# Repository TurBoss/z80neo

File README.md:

# z80neo

```

          ████   ████                             
         █░░░ █ █░░░██                            
  ██████░█   ░█░█  █░█ ███████   █████   ██████   
 ░░░░██ ░ ████ ░█ █ ░█░░██░░░██ ██░░░██ ██░░░░██  
    ██   █░░░ █░██  ░█ ░██  ░██░███████░██   ░██  
   ██   ░█   ░█░█   ░█ ░██  ░██░██░░░░ ░██   ░██  
  ██████░ ████ ░ ████  ███  ░██░░██████░░██████   
 ░░░░░░  ░░░░   ░░░░  ░░░   ░░  ░░░░░░  ░░░░░░    

```

**A computer built around a real Z80 CPU.**

z80neo is not an emulator. A genuine Zilog **Z0840004** (NMOS, TTL-level)
runs real code, while an Olimex **RP2350-PICO2-BB48** (RP2350**B**, 48 GPIOs)
acts as its RAM, ROM and *all* of its I/O. The Pico captures the Z80 bus
cycle-by-cycle through PIO, services each access and stalls the CPU with
`WAIT` — so the two chips share one bus exactly like a classic microcomputer.

On top of that it emulates an MMU, a serial console (and a second UART), a
15-drive CP/M sector disk, an OLED status display, a keypad menu, and it
drives an optional FPGA VDP over SPI. It boots **CP/M 2.2**, **Fuzix** and
bare-metal Z80 programs from an SD card.

- Website / source: https://github.com/turboss/z80neo
- Console: **UART0, 115200 8N1** (GPIO0/1), shared by the firmware and CP/M
- Storage: SD card (FatFS) holding the OS images, disk images and `Z80NEO.INI`

## Features

- **Real Z80, no emulation** — the Pico is bus master/slave only; the Z80
  executes every instruction.
- **Full memory + MMU** — four 16 KB banks (`ram[4][16384]`), optionally
  extended with PSRAM, behind a 4-page MMU on ports `0xF0`–`0xF3`.
- **Serial console** on UART0 (`0x80`/`0x81`) plus an independent second UART
  (UART1, `0x90`–`0x93`) with runtime-configurable baud/format.
- **CP/M 2.2** with 15 emulated sector disks (A:–O:) from `CPMDISK0..14.IMG`.
- **SD-card file API** for bare-metal programs (`0xA0`–`0xA7`), with directory
  walking into subdirectories.
- **Firmware-side Standard MIDI File player** streaming to a UART1 MIDI out,
  with a live VT102 channel monitor.
- **SSD1306 OLED status display + ADC keypad menu**, with an idle screensaver.
- **VoidVDP / NullVDP support** — a 640×256 bitmap console with an `ESC g`
  protocol, mirrored over SPI to an FPGA VDP.

## Hardware

- CPU: Zilog **Z0840004** (NMOS Z80, 4 MHz rated, run at ~128 kHz)
- Host: Olimex **RP2350-PICO2-BB48** (RP2350B, 48-GPIO package, 16 MB flash)
- Z80 clock generated by PIO on **GPIO32**, reset on **GPIO33**
- SD card interface
- Serial port (UART0, 115200 8N1, GPIO0/1)
- Second UART on **GPIO38 (TX) / GPIO39 (RX)**
- SSD1306 OLED (I2C1) and an ADC keypad
- Optional NullVDP on an FPGA over SPI (GPIO34–37)

Schematics live in `hardware/`; see the pinout and datasheets in `doc/`.

## Schematics

## How it works

- **Bus capture (PIO)** — two PIO0 state machines watch `MREQ` and `IORQ`. On
  a cycle they assert `WAIT`, push a bus snapshot to the FIFO and block on
  `PULL`. The ARM core services the cycle, reads the address/data through the
  `SEL1/2/3` mux and releases `WAIT`. Because the Z80 is stalled for the whole
  service time, timing is independent of the emulated clock speed.
- **Memory / MMU** — `src/memory.c`. 16-bit addresses map through `mmu_page[]`
  into the 16 KB banks; PSRAM can extend them.
- **I/O ports** — handled in `io_read_port()` / `io_write_port()`:

  | Port(s) | Function |
  |---------|----------|
  | `0x80`/`0x83` | console data |
  | `0x81` | console status |
  | `0x90`/`0x91` | UART1 data / status |
  | `0x92`/`0x93` | UART1 baud code / line format config |
  | `0x94`/`0x95` | NullVDP console byte / link status |
  | `0xA0`–`0xA7` | SD-card file API (command, name, data, seek/size) |
  | `0xD1` | I2C EEPROM |
  | `0xE0`–`0xE3` | CP/M disk (data/command, track, sector/status, drive select) |
  | `0xF0`–`0xF3` | MMU page select |

- **Clock / reset** — `src/z80clock.pio` generates the Z80 clock; frequency
  (`Z80_KHZ`, 32..1000) and duty (`Z80_DUTY`, 5..95 %) are settable from
  `Z80NEO.INI`.
- **Display / keys** — core 1 drives the OLED and the debounced ADC keypad
  menu; core 0 owns the bus loop and UARTs.
- **Boot** — mount SD → read `Z80NEO.INI` → load the Intel HEX program into
  banks → hold reset → start PIO → release reset.

See `AGENTS.md` for an in-depth description of every subsystem and the
hardware/timing gotchas.

## Build the firmware

Requires the Raspberry Pi **pico-sdk 2.x** and an `arm-none-eabi` toolchain.
`firmware/build.sh` hardcodes the local SDK paths — edit it for your setup.

```sh
cd firmware
./build.sh            # cmake -B build -S . -DPICO_BOARD=z80neo_bb48 -DPSRAM_ENABLE=ON
```

The output ELF is `firmware/build/z80neo/z80neo.elf`. **Build with
`PICO_BOARD=z80neo_bb48`, never `pico2`** — `pico2` is the RP2350A (30 GPIOs),
so GPIO30–47 (clock, reset, keypad) are silently dropped. `main.c` `#error`s on
the wrong package.

Flash over CMSIS-DAP/OpenOCD:

```sh
cd firmware
./upload.sh           # openocd ... program build/z80neo/z80neo.elf verify reset exit
```

Debug (OpenOCD + GDB):

```sh
cd firmware
./debug.sh            # standard gdbinit
./debug.sh serial     # serial-tracing gdb script
```

There is no unit-test framework; verify by building, flashing and watching
UART0 (115200 8N1) plus the OLED. `tools/z80_boot_sim.py` is the only offline
harness. The full pipeline — firmware + OS + SD deploy — is `./build_all.sh`.

## SD card

Copy `sdcard/Z80NEO.INI`, your program image and the CP/M disk images to the
card root. The preferred INI format is order-independent `KEY=VALUE`:

| Key | Meaning |
|-----|---------|
| `MACHINE` | machine name |
| `CANCEL2`,`CANCEL`,`OK`,`BACK`,`DOWN`,`UP` | ADC keypad thresholds |
| `PROG1`..`PROG4` | program filenames (`PROG1` is loaded at boot) |
| `DEBUG` | `1` = hold in a busy loop at boot |
| `FUZIX` | full-RAM load + hardware `/INT` (Fuzix) |
| `BAUD` | UART0 console baud (default 115200) |
| `UART1_BAUD`, `UART1_FORMAT` | second UART, e.g. `115200` / `8N1` |
| `Z80_KHZ`, `Z80_DUTY` | Z80 clock frequency / duty |
| `MIDI_GROUP_X10`, `MIDI_BYTE_X10` | MIDI player speed trim (tenths of a ms) |
| `MIDI_PANEL` | `1`/`0` firmware MIDI channel monitor |
| `SCREENSAVER`, `SS_MODE`, `SS_IDLE` | idle OLED screensaver settings |

The default `sdcard/Z80NEO.INI` boots CP/M. Program images are Intel HEX —
both the `.hex` (CP/M) and `.ihx` (z88dk) spellings load.

## Software

- **CP/M 2.2** — `software/cpm/z80neo/`, built with `make` into
  `build/cpmz80neo.hex`. CCP/BDOS at `0xD400`, BIOS at `0xEB00`; 15 sector
  disks A:–O: from `CPMDISK0..14.IMG`. CP/M disk helpers live in `tools/`
  (`pack_cpm_collection.py`, `install_cpm_disks.py`) and the PySide6
  `TBCPMTools` GUI can inspect/edit the images.
- **Fuzix** — `software/Fuzix/`, an FCC-built banked kernel.
- **CP/M software** — `software/cpm/` also holds `turboterm/` (`TTERM.COM`,
  bridges the CP/M console to UART1), the `midiplayer/`, a `regulus-radiant-crucible/`
  Forth, and the `te/` editor sources.
- **BASIC** — BBC BASIC (`software/bbcbasic{, -z80}/`) and
  `software/Tiny-Basic-Z80/`.
- **Bare-metal C (`zcc +z80neo`)** — the in-tree z88dk target links at
  `ORG 0x0000`, owns page 0 and uses ports `0x80`/`0x81`. It ships a
  bitmap graphics layer (`z80neo_gfx_*`) speaking the VDP `ESC g` protocol.
  See `software/z80neo/`.
- **MON** — `software/z80neo/monitor/`, a full machine monitor/debugger
  (dump/edit, disassemble, breakpoints, single-step, HEX load, MMU control).
- **MIDI player** — `software/z80neo/midiplayer/` (bare metal) and
  `software/cpm/midiplayer/` (`MIDI.COM`): SD-card Standard MIDI File players
  driving UART1 at 31250 baud, with a firmware-side SMF parser and monitor.
- **Assembly tests** — `software/asm/`, built with z88dk
  (`./build_hex.sh <name>`).

### Assembly example

```asm
PORT_LEDS: equ 0x40
VAL_A equ 0xBA
VAL_B equ 0xAB

main:
  ld	sp, 0x3fff

loop:
  ld    A, VAL_A
  out	(PORT_LEDS), A

  ld    A, VAL_B
  out	(PORT_LEDS), A

  JP	loop

topOfStack
```

## Companions

- **VoidVDP** (`vdp/`) — a fork of VersaTerm used as a standalone RP2350/RP2040
  **VGA** serial terminal (a separate board). Talks over UART1 and implements
  the console protocol in `doc/vdp_protocol.md`.
- **NullVDP** (`vdp/NullVDP/`) — a Verilog VDP on a Sipeed Tang Primer 20K
  FPGA with HDMI output, spoken to over **SPI** by the firmware.
- **sdl_client** (`sdl_client/`) — a PC-side SDL3 **VT100/VT102** terminal for
  `/dev/ttyACM0`, including the `ESC g` bitmap layer.

## Pictures

the thing

back wiring

pulse view capture

display

serial out

## Community

Join the live chat:

- Matrix: https://matrix.to/#/#z80neo:jauriarts.org
- Discord: https://discord.gg/TQudWKCKCQ
- IRC: https://web.libera.chat/ **#z80neo**

## References

- picoram6116 — https://github.com/lambdamikel/picoram6116
- Agonlight - https://www.thebyteattic.com/p/agon.html
- Neo6502 — https://neo6502.com/

## License

- Hardware: CERN Open Hardware Licence Version 2 — Strongly Reciprocal
- Software: GPL v3
- Documentation: CC BY-SA 4.0

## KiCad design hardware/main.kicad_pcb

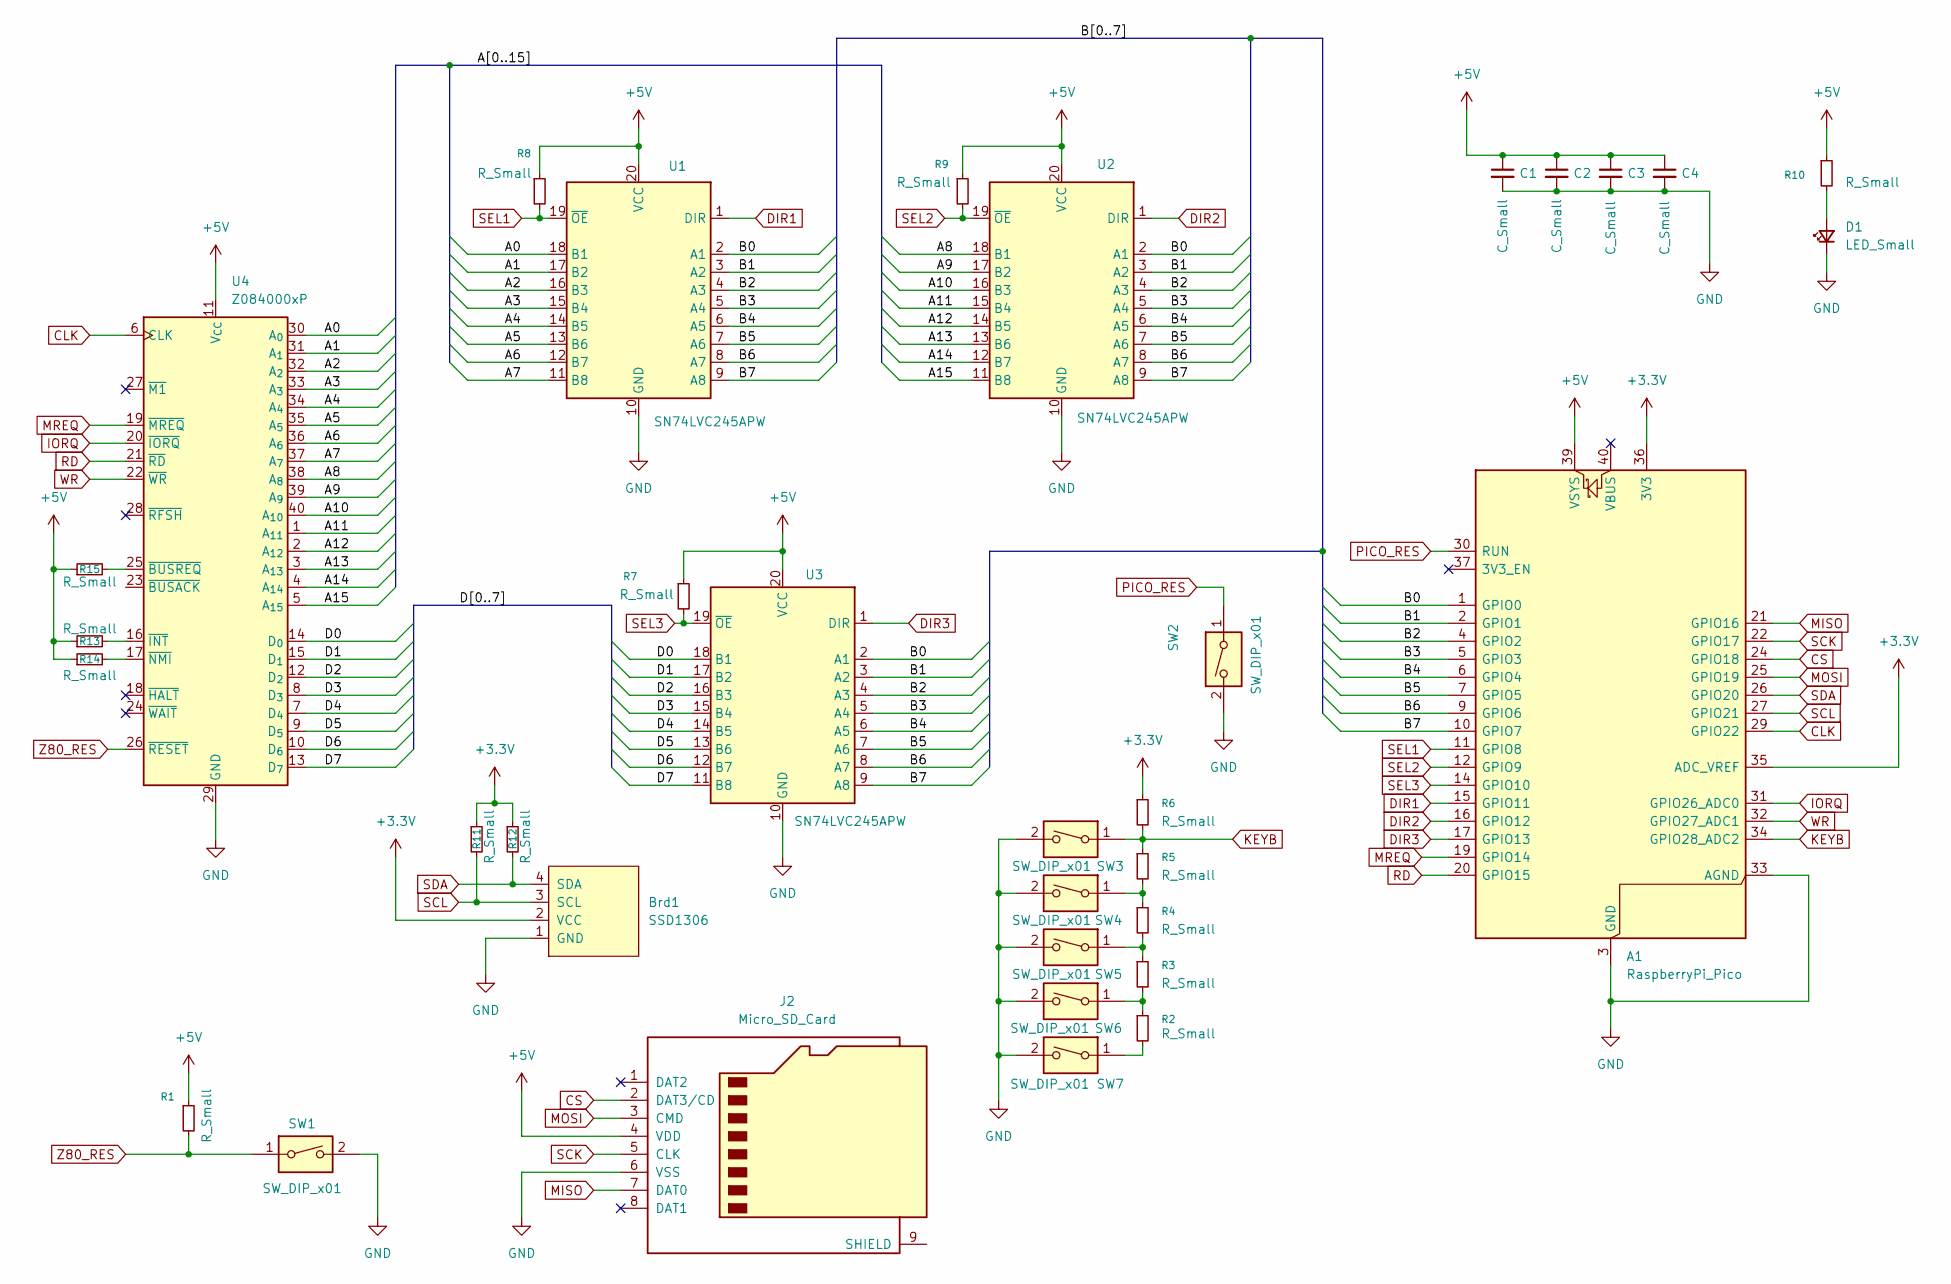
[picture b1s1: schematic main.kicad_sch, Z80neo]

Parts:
A1: RaspberryPi_Pico; RaspberryPi_Pico_Common_Unspecified
Brd1: SSD1306; Adafruit_SSD1306_No_Mounting_Holes
C1, C2, C3, C4: C_Small; C_Disc_D4.3mm_W1.9mm_P5.00mm
D1: LED_Small; LED_D3.0mm
J2: Micro_SD_Card; PinSocket_1x08_P2.54mm_Horizontal
R1, R2, R3, R4, R5, R6, R7, R8, R9, R10, R11, R12, R13, R14, R15: R_Small; R_Axial_DIN0207_L6.3mm_D2.5mm_P7.62mm_Horizontal
SW1, SW2, SW3, SW4, SW5, SW6, SW7: SW_DIP_x01; SW_PUSH_6mm
U1, U2, U3: SN74LVC245APW; CERDIP-20_W7.62mm_SideBrazed_LongPads_Socket
U4: Z084000xP; DIP-40_W15.24mm

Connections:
+3.3V: A1.35 (ADC_VREF), A1.36 (3V3), Brd1.2 (VCC), R6.1, R11.1, R12.1
+5V: A1.39 (VSYS), C1.1, C2.1, C3.1, C4.1, J2.4 (VDD), R1.1, R7.1, R8.1, R9.1, R10.1, R13.1, R14.1, R15.1, U1.20 (VCC), U2.20 (VCC), U3.20 (VCC), U4.11 (V_{CC})
/A0: U1.18 (B1), U4.30 (A_{0})
/A1: U1.17 (B2), U4.31 (A_{1})
/A2: U1.16 (B3), U4.32 (A_{2})
/A3: U1.15 (B4), U4.33 (A_{3})
/A4: U1.14 (B5), U4.34 (A_{4})
/A5: U1.13 (B6), U4.35 (A_{5})
/A6: U1.12 (B7), U4.36 (A_{6})
/A7: U1.11 (B8), U4.37 (A_{7})
/A8: U2.18 (B1), U4.38 (A_{8})
/A9: U2.17 (B2), U4.39 (A_{9})
/A10: U2.16 (B3), U4.40 (A_{10})
/A11: U2.15 (B4), U4.1 (A_{11})
/A12: U2.14 (B5), U4.2 (A_{12})
/A13: U2.13 (B6), U4.3 (A_{13})
/A14: U2.12 (B7), U4.4 (A_{14})
/A15: U2.11 (B8), U4.5 (A_{15})
/B0: A1.1 (GPIO0), U1.2 (A1), U2.2 (A1), U3.2 (A1)
/B1: A1.2 (GPIO1), U1.3 (A2), U2.3 (A2), U3.3 (A2)
/B2: A1.4 (GPIO2), U1.4 (A3), U2.4 (A3), U3.4 (A3)
/B3: A1.5 (GPIO3), U1.5 (A4), U2.5 (A4), U3.5 (A4)
/B4: A1.6 (GPIO4), U1.6 (A5), U2.6 (A5), U3.6 (A5)
/B5: A1.7 (GPIO5), U1.7 (A6), U2.7 (A6), U3.7 (A6)
/B6: A1.9 (GPIO6), U1.8 (A7), U2.8 (A7), U3.8 (A7)
/B7: A1.10 (GPIO7), U1.9 (A8), U2.9 (A8), U3.9 (A8)
/D0: U3.18 (B1), U4.14 (D_{0})
/D1: U3.17 (B2), U4.15 (D_{1})
/D2: U3.16 (B3), U4.12 (D_{2})
/D3: U3.15 (B4), U4.8 (D_{3})
/D4: U3.14 (B5), U4.7 (D_{4})
/D5: U3.13 (B6), U4.9 (D_{5})
/D6: U3.12 (B7), U4.10 (D_{6})
/D7: U3.11 (B8), U4.13 (D_{7})
CLK: A1.29 (GPIO22), U4.6 (CLK)
CS: A1.24 (GPIO18), J2.2 (DAT3/CD)
DIR1: A1.15 (GPIO11), U1.1 (DIR)
DIR2: A1.16 (GPIO12), U2.1 (DIR)
DIR3: A1.17 (GPIO13), U3.1 (DIR)
GND: A1.3 (GND), A1.8 (GND), A1.13 (GND), A1.18 (GND), A1.23 (GND), A1.28 (GND), A1.33 (AGND), A1.38 (GND), Brd1.1 (GND), C1.2, C2.2, C3.2, C4.2, D1.1 (K), J2.6 (VSS), SW1.2, SW2.2, SW3.2, SW4.2, SW5.2, SW6.2, SW7.2, U1.10 (GND), U2.10 (GND), U3.10 (GND), U4.29 (GND)
IORQ: A1.31 (GPIO26_ADC0), U4.20 (~IORQ)
KEYB: A1.34 (GPIO28_ADC2), R5.1, R6.2, SW3.1
MISO: A1.21 (GPIO16), J2.7 (DAT0)
MOSI: A1.25 (GPIO19), J2.3 (CMD)
MREQ: A1.19 (GPIO14), U4.19 (~MREQ)
unnamed: D1.2 (A), R10.2
unnamed: R2.1, R3.2, SW6.1
unnamed: R2.2, SW7.1
unnamed: R3.1, R4.2, SW5.1
unnamed: R4.1, R5.2, SW4.1
unnamed: R15.2, U4.25 (~BUSREQ)
unnamed: R13.2, U4.16 (~INT)
unnamed: R14.2, U4.17 (~NMI)
PICO_RES: A1.30 (RUN), SW2.1
RD: A1.20 (GPIO15), U4.21 (~RD)
SCK: A1.22 (GPIO17), J2.5 (CLK)
SCL: A1.27 (GPIO21), Brd1.3 (SCL), R11.2
SDA: A1.26 (GPIO20), Brd1.4 (SDA), R12.2
SEL1: A1.11 (GPIO8), R8.2, U1.19 (~OE)
SEL2: A1.12 (GPIO9), R9.2, U2.19 (~OE)
SEL3: A1.14 (GPIO10), R7.2, U3.19 (~OE)
WR: A1.32 (GPIO27_ADC1), U4.22 (~WR)
Z80_RES: R1.2, SW1.1, U4.26 (~RESET)

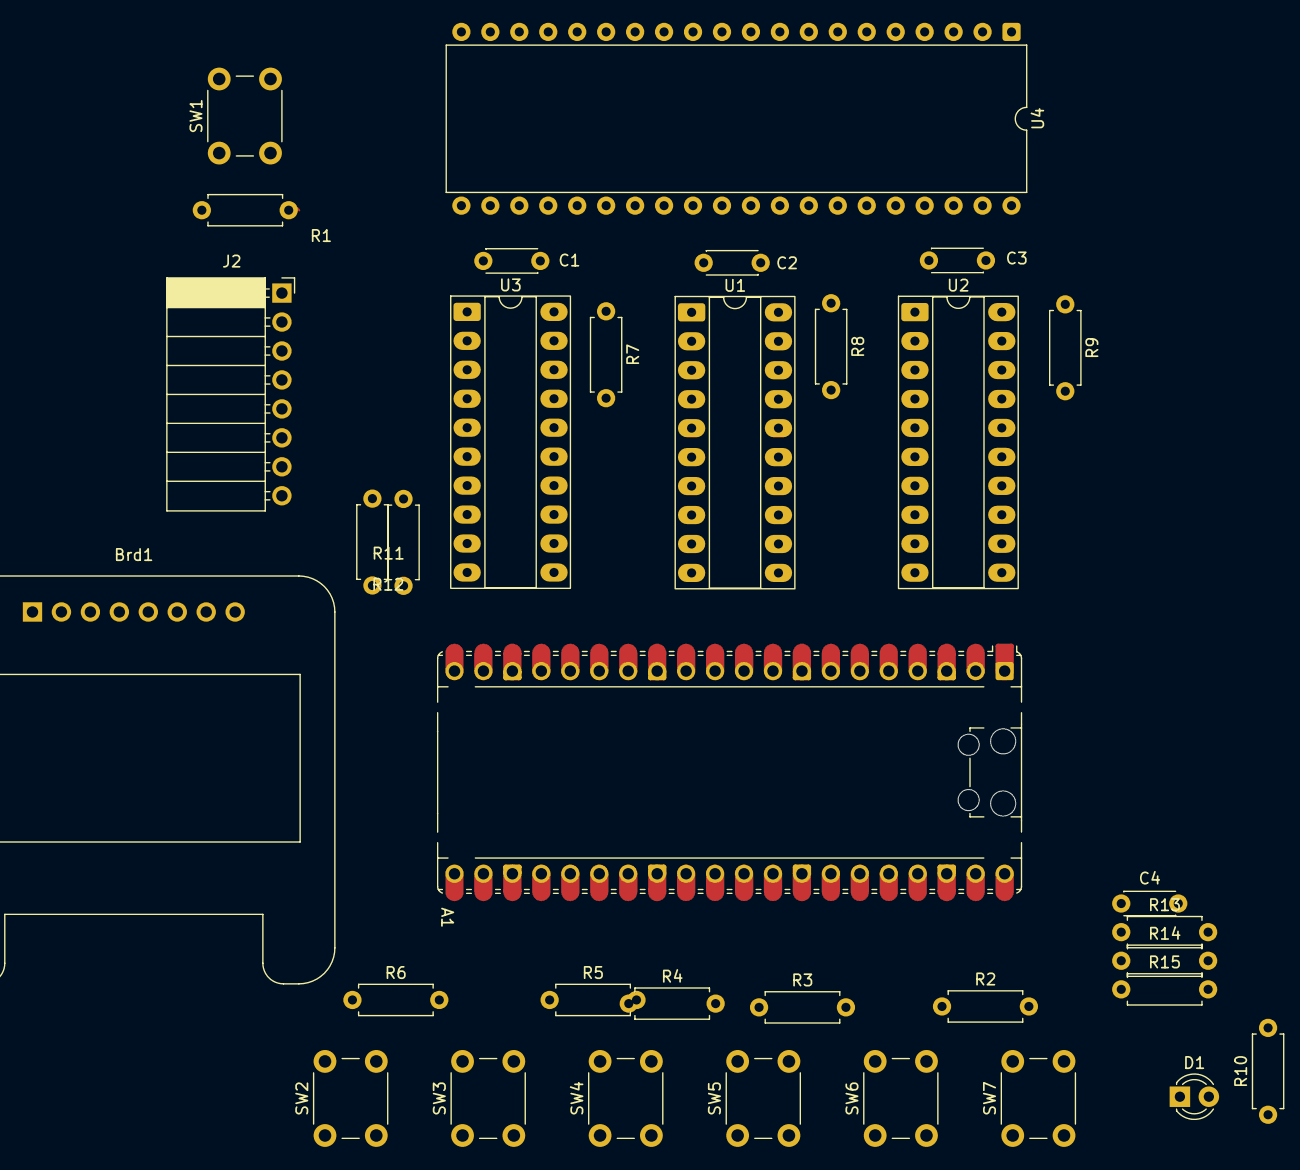
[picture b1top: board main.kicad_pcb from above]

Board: 2 copper layers, 34 parts (0 on the bottom side), 63 nets.

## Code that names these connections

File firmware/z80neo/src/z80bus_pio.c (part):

// z80bus_pio.c — PIO-accelerated Z80 bus handler (dual-SM capture)
// SM0 (mem_sm=0): JMP_PIN = GPIO20 (MREQ), SET pin = GPIO5  -> Z80 WAIT (pin 24)
// SM1 (io_sm=1):  JMP_PIN = GPIO22 (IORQ), SET pin = GPIO4 -> Z80 WAIT (pin 24)
//
// The PIO asserts WAIT the moment a bus cycle starts and holds the Z80 stalled
// until the ARM has serviced the cycle, then releases WAIT and waits for the
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// Per-cycle trace.  `kind`: 0=mem rd, 1=mem wr, 2=io rd, 3=io wr,
// 4=refresh skip, 5=io glitch/M1 skip.  `pc0`/`pc1` are the mem/io PIO SM
// program counters sampled while the cycle is serviced, so a stuck SM shows up
// as a constant PC.  `ctl` is the live control-line snapshot (bit0 MREQ,
// bit1 RD, bit2 IORQ, bit3 WR; a set bit means the line was HIGH/inactive).
typedef struct {
    uint32_t t_us;
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volatile diag_cyc_t diag_cyc[DIAG_CYC_N];
volatile uint32_t diag_cyc_idx = 0;

volatile uint32_t diag_mem_timeouts = 0;   // MREQ never went HIGH in handle_mem
volatile uint32_t diag_io_timeouts  = 0;   // RD/WR never asserted in handle_iorq
volatile uint32_t diag_m1_skips     = 0;   // io SM fired on an M1 fetch
volatile uint32_t diag_max_service_us = 0;
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        diag_record(5, 0, 0);
        return;
    }
    // PIO holds WAIT (GPIO4=0) — Z80 is stopped
    gpio_put(SEL3_OUT, 1); gpio_put(SEL1_OUT, 1); gpio_put(SEL2_OUT, 1);
    gpio_set_dir_masked(bus_mask, 0);
    // Wait for WR or RD to assert (sampled during T2/TW, Z80 is stalled)
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
static void handle_mem(void) {
    uint32_t t0 = time_us_32();
    // PIO holds WAIT (GPIO5=0) — Z80 is stopped.
    //
    // A Z80 refresh cycle asserts MREQ (RFSH is not wired on this board) but
    // neither RD nor WR, so the mem SM fires on it.  Wait here for RD/WR to
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    if (!pio_active) return 0; uint32_t d = 0;
    // Process I/O cycles first.  During an M1 (opcode fetch) both SMs fire;
    // servicing the io SM first lets handle_iorq see MREQ still LOW and skip
    // the fetch, releasing its WAIT (GPIO4) before handle_mem runs.  If memory
    // were serviced first, handle_mem would wait for MREQ to go HIGH while the
    // io SM still held WAIT, stalling 20 ms and then releasing the data bus
    // before the Z80 could latch the opcode.
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    uint off_mem = pio_add_program(bus_pio, &z80bus_pio_mem_program);
    uint off_io  = pio_add_program(bus_pio, &z80bus_pio_io_program);

    // MEM SM: JMP_PIN=20 (MREQ), SET pins=GPIO5
    pio_sm_config cm = z80bus_pio_mem_program_get_default_config(off_mem);
    sm_config_set_in_pins(&cm, 12);
    sm_config_set_set_pins(&cm, 5, 1);
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    pio_sm_init(bus_pio, mem_sm, off_mem, &cm);
    pio_sm_set_enabled(bus_pio, mem_sm, true);

    // I/O SM: JMP_PIN=22 (IORQ), SET pins=GPIO4
    pio_sm_config ci = z80bus_pio_io_program_get_default_config(off_io);
    sm_config_set_in_pins(&ci, 12);
    sm_config_set_set_pins(&ci, 4, 1);
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
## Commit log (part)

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2025-11-07 Add LIC file
2025-11-07 add a shell script to build the z80 programs
2025-11-07 add some details to readme
2025-11-07 add PDF schematics
2025-11-07 add schematic image and more references
2025-11-07 README tweak
2025-11-07 remove files from build
2025-11-07 add pico_fatfs as submodule
2025-11-07 added missing lines to iorq and wr in the schematic and SD ini file
2025-11-08 start implement usb serial
2025-11-09 Add pictures
2025-11-09 add asm example to readme
2025-11-09 add logo and description
2025-11-09 upload small logo and add links
2025-11-09 fix link
2025-11-09 ignore ide files
2025-11-12 rename src firectory to firmware
2025-11-12 tmp hax
2025-11-12 readd pico_fatfs
2025-11-12 add a cool text :)
2025-11-12 Add empty line
2025-11-12 fix typo on readme and add irc
2025-11-12 add discord and irc links to readme
2025-11-12 clean software directory and ignore bin files
2025-11-14 update pcb files
2025-11-15 pcb routing
2025-11-15 update readme schematic
2025-11-16 fix osc
2025-11-16 minor
2025-11-17 fix freq
2025-11-17 change freq to 200Hz
2025-11-17 fix osc to 8 Khz
2025-11-17 clock pi to 300mhz
2025-11-19 re think memory and device io
2025-11-20 disable overclock, back to 150Mhz and add i2c display to schematic
2025-11-22 receive characters on the z80
2025-11-22 ignore object files .o
2025-11-22 use tht components
2025-11-24 add serial status port
2026-02-09 Pico2 BB48 Olimex port
2026-03-09 MMU pat 1
2026-05-24 latest changes
